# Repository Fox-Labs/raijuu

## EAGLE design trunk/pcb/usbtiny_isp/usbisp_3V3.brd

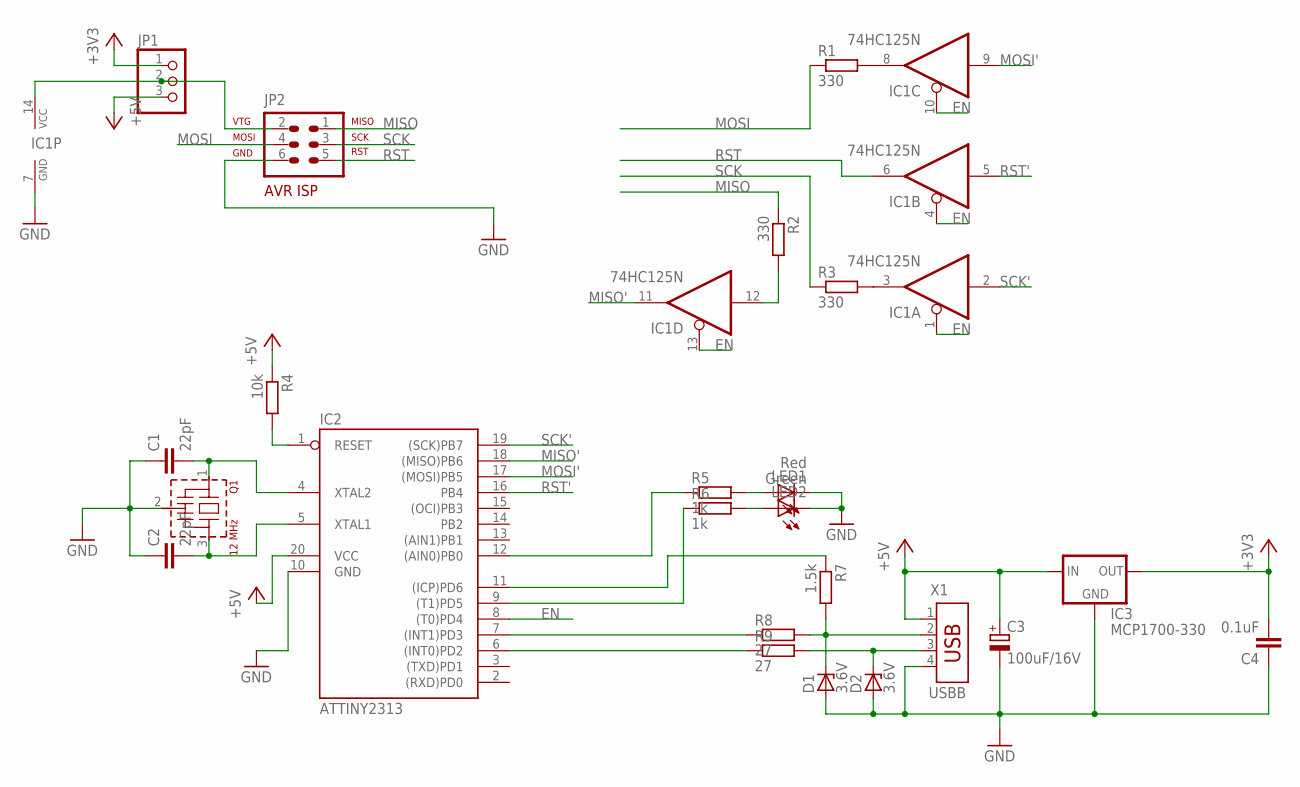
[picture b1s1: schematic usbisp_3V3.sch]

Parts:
C1, C2: 22pF; C025-025X050
C3: 100uF/16V; E2,5-6
C4: 0.1uF; C025-025X050
D1, D2: 3.6V; DO41Z10
IC1: 74HC125N; DIL14
IC2: ATTINY2313; DIL20
IC3: MCP1700-330
JP1: PINHD-1X3; 1X03
JP2: AVR-ISP-6
LED1: Red; LED3MM
LED2: Green; LED3MM
Q1: 12 MHz; CSTLS_G9
R1, R2, R3: 330; 0207/7
R4: 10k; 0207/7
R5, R6: 1k; 0207/7
R7: 1.5k; 0207/7
R8, R9: 27; 0207/7
X1: USBB; USB-B

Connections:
+3V3: C4.2, IC3.OUT, JP1.1
+5V: C3.+, IC2.20 (VCC), IC3.IN, JP1.3, R4.1, X1.1
EN: IC1.1 (OE), IC1.4 (OE), IC1.10 (OE), IC1.13 (OE), IC2.8 ((T0)PD4)
GND: C1.1, C2.1, C3.-, C4.1, D1.A, D2.A, IC1.7 (GND), IC2.10 (GND), IC3.GND, JP2.6 (GND), LED1.K (C), LED2.K (C), Q1.2 (VSS), X1.4
MISO: JP2.1 (MISO), R2.1
MISO': IC1.11 (O), IC2.18 ((MISO)PB6)
MOSI: JP2.4 (MOSI), R1.1
MOSI': IC1.9 (I), IC2.17 ((MOSI)PB5)
unnamed: C1.2, IC2.4 (XTAL2), Q1.1
unnamed: C2.2, IC2.5 (XTAL1), Q1.3
unnamed: IC2.6 ((INT0)PD2), R9.1
unnamed: IC2.7 ((INT1)PD3), R8.1
unnamed: D2.C, R9.2, X1.3
unnamed: D1.C, R7.2, R8.2, X1.2
unnamed: IC2.11 ((ICP)PD6), R7.1
unnamed: IC2.9 ((T1)PD5), R6.1
unnamed: IC2.12 ((AIN0)PB0), R5.1
unnamed: LED2.A, R6.2
unnamed: LED1.A, R5.2
unnamed: IC2.1 (RESET), R4.2
unnamed: IC1.14 (VCC), JP1.2, JP2.2 (VTG)
unnamed: IC1.12 (I), R2.2
unnamed: IC1.3 (O), R3.2
unnamed: IC1.8 (O), R1.2
RST: IC1.6 (O), JP2.5 (RST)
RST': IC1.5 (I), IC2.16 (PB4)
SCK: JP2.3 (SCK), R3.1
SCK': IC1.2 (I), IC2.19 ((SCK)PB7)

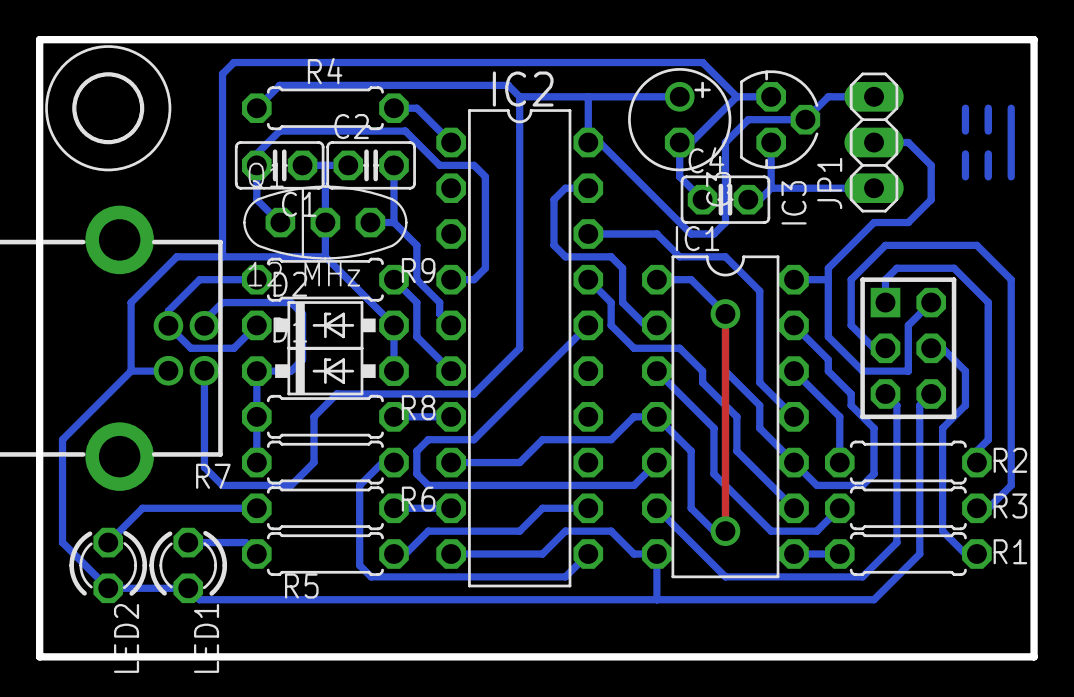
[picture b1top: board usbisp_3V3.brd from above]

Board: 2 copper layers, 55.2 x 34.3 mm, 26 parts (0 on the bottom side), 28 nets.

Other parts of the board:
U$4: 3,6
U$5: LOGO-COPPER
